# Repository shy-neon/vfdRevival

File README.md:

# VFD-Revival

<div style="display: flex">

</div>
<br>
Although many ICs for driving VFD displays exist, they are generally out of production, or even out of stock. Many can be found on Ebay but usually they are very expensive and New Old Stock soviet ICs. The main goal of this project is to drive those tubes with jellybeans ICs, which can be easily sourced at reasonables proces. The repo proveides an example sketch, schematics and pcb layouts.

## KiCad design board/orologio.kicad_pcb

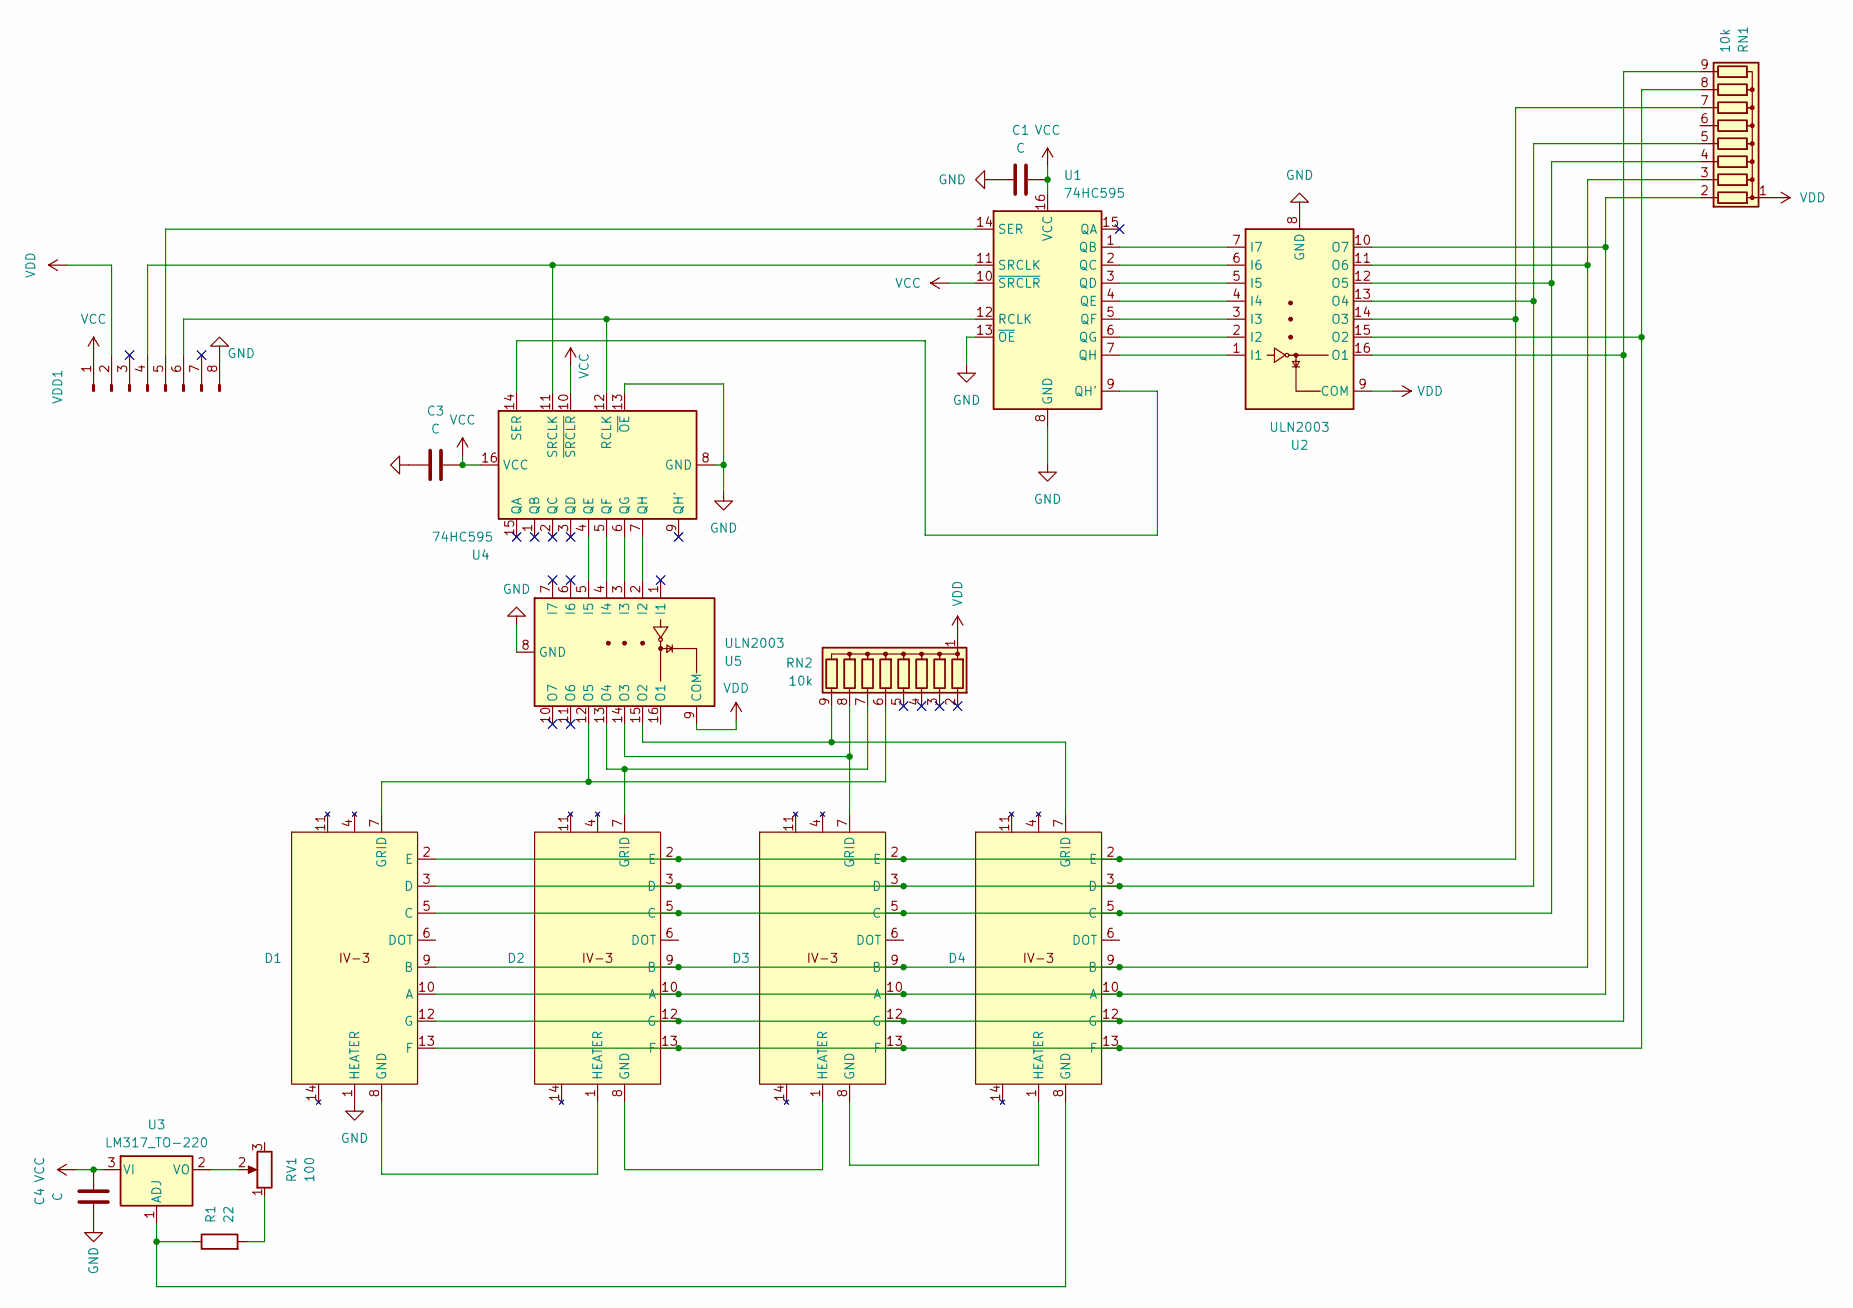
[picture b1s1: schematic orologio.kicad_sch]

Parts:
C1, C3, C4: C; C_Disc_D3.4mm_W2.1mm_P2.50mm
D1, D2, D3, D4: IV-3
R1: 22; R_Axial_DIN0204_L3.6mm_D1.6mm_P1.90mm_Vertical
RN1, RN2: 10k; R_Array_SIP9
RV1: 100; Potentiometer_Piher_PT-6-V_Vertical
U1, U4: 74HC595; DIP-16_W7.62mm_Socket_LongPads
U2, U5: ULN2003; DIP-16_W7.62mm_Socket_LongPads
U3: LM317_TO-220; TO-220-3_Vertical
VDD1: Conn_01x08_Pin; PinHeader_1x08_P2.54mm_Vertical

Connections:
GND: C1.1, C3.1, C4.2, D1.1 (HEATER), U1.8 (GND), U1.13 (~OE), U2.8 (GND), U4.8 (GND), U4.13 (~OE), U5.8 (GND), VDD1.8
unnamed: D1.10 (A), D2.10 (A), D3.10 (A), D4.10 (A), RN1.2 (R1), U2.10 (O7)
unnamed: D1.9 (B), D2.9 (B), D3.9 (B), D4.9 (B), RN1.3 (R2), U2.11 (O6)
unnamed: D1.5 (C), D2.5 (C), D3.5 (C), D4.5 (C), RN1.4 (R3), U2.12 (O5)
unnamed: D1.3 (D), D2.3 (D), D3.3 (D), D4.3 (D), RN1.5 (R4), U2.13 (O4)
unnamed: D1.2 (E), D2.2 (E), D3.2 (E), D4.2 (E), RN1.7 (R6), U2.14 (O3)
unnamed: D1.13 (F), D2.13 (F), D3.13 (F), D4.13 (F), RN1.8 (R7), U2.15 (O2)
unnamed: D1.12 (G), D2.12 (G), D3.12 (G), D4.12 (G), RN1.9 (R8), U2.16 (O1)
unnamed: D1.8 (GND), D2.1 (HEATER)
unnamed: D1.7 (GRID), RN2.6 (R5), U5.12 (O5)
unnamed: D2.8 (GND), D3.1 (HEATER)
unnamed: D2.7 (GRID), RN2.7 (R6), U5.13 (O4)
unnamed: D3.8 (GND), D4.1 (HEATER)
unnamed: D3.7 (GRID), RN2.8 (R7), U5.14 (O3)
unnamed: D4.8 (GND), R1.1, U3.1 (ADJ)
unnamed: D4.7 (GRID), RN2.9 (R8), U5.15 (O2)
unnamed: R1.2, RV1.1
unnamed: U1.1 (QB), U2.7 (I7)
unnamed: U1.2 (QC), U2.6 (I6)
unnamed: U1.3 (QD), U2.5 (I5)
unnamed: U1.4 (QE), U2.4 (I4)
unnamed: U1.5 (QF), U2.3 (I3)
unnamed: U1.6 (QG), U2.2 (I2)
unnamed: U1.9 (QH'), U4.14 (SER)
unnamed: U1.7 (QH), U2.1 (I1)
unnamed: U1.12 (RCLK), U4.12 (RCLK), VDD1.6
unnamed: U1.14 (SER), VDD1.5
unnamed: U1.11 (SRCLK), U4.11 (SRCLK), VDD1.4
unnamed: RV1.2, U3.2 (VO)
unnamed: U4.4 (QE), U5.5 (I5)
unnamed: U4.5 (QF), U5.4 (I4)
unnamed: U4.6 (QG), U5.3 (I3)
unnamed: U4.7 (QH), U5.2 (I2)
VCC: C1.2, C3.2, C4.1, U1.10 (~SRCLR), U1.16 (VCC), U3.3 (VI), U4.10 (~SRCLR), U4.16 (VCC), VDD1.1
VDD: RN1.1 (common), RN2.1 (common), U2.9 (COM), U5.9 (COM), VDD1.2

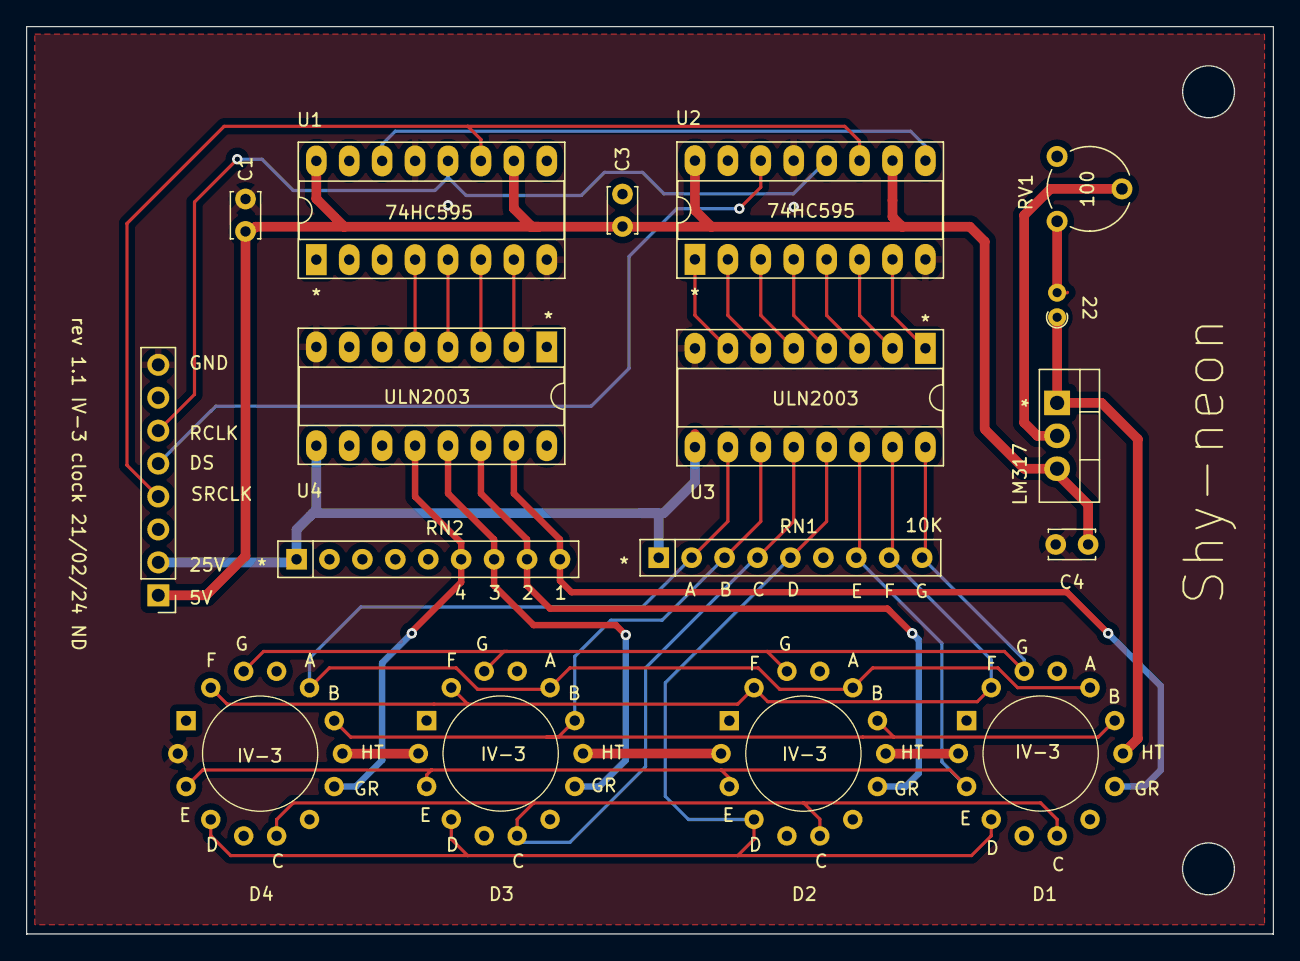
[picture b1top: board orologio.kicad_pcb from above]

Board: 2 copper layers, 96.2 x 70.0 mm, 17 parts (0 on the bottom side), 35 nets.

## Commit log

2025-05-22 images
2025-05-22 board
